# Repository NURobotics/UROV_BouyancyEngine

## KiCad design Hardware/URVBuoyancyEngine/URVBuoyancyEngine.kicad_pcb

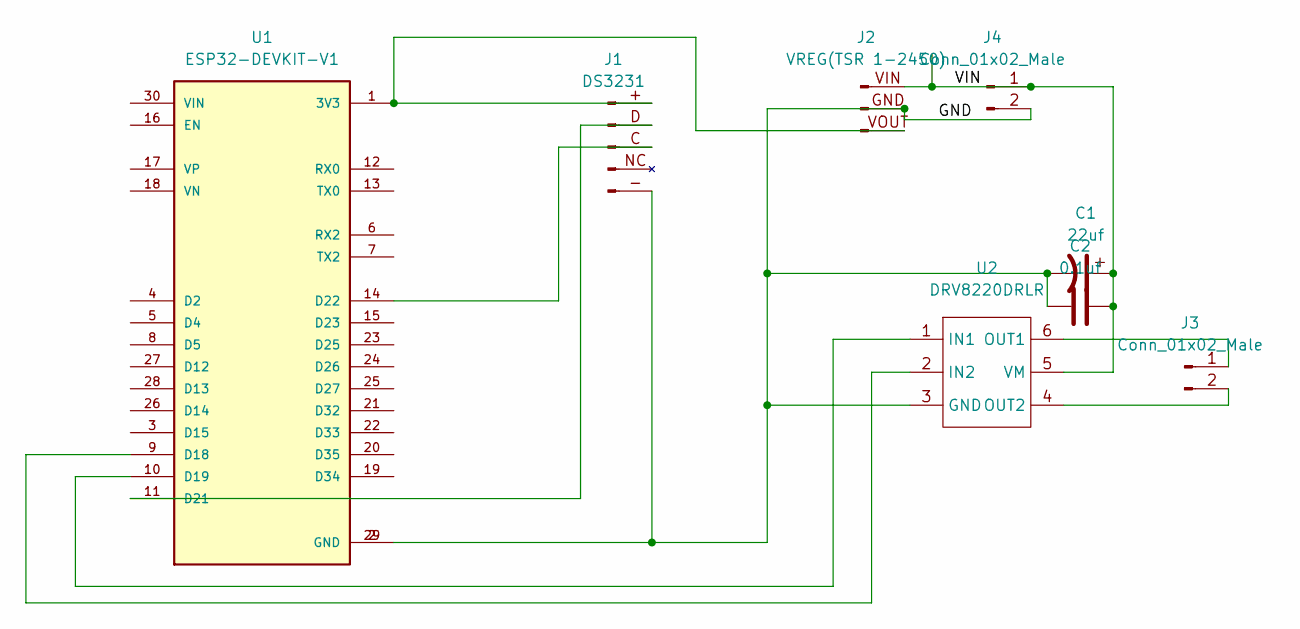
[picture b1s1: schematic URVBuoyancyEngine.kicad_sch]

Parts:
C1: 22uf; CP_Elec_5x5.7
C2: 0.1uf; C_0603_1608Metric
J1: DS3231; PinHeader_1x05_P2.54mm_Vertical
J2: VREG(TSR 1-2450); PinHeader_1x03_P2.54mm_Vertical
J3, J4: Conn_01x02_Male; PinHeader_1x02_P2.54mm_Vertical
U1: ESP32-DEVKIT-V1; MODULE_ESP32_DEVKIT_V1; PARTREV N/A
U2: DRV8220DRLR; SOT-563

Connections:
/GND: C1.2, C2.2, J1.- (5), J2.GND, J4.2, U1.2 (GND), U1.29 (GND), U2.3 (GND)
/VIN: C1.1, C2.1, J2.VIN, J4.1, U2.5 (VM)
unnamed: J1.+ (1), J2.VOUT, U1.1 (3V3)
unnamed: J1.C (3), U1.14 (D22)
unnamed: J1.D (2), U1.11 (D21)
unnamed: J3.1, U2.6 (OUT1)
unnamed: J3.2, U2.4 (OUT2)
unnamed: U1.9 (D18), U2.2 (IN2)
unnamed: U1.10 (D19), U2.1 (IN1)

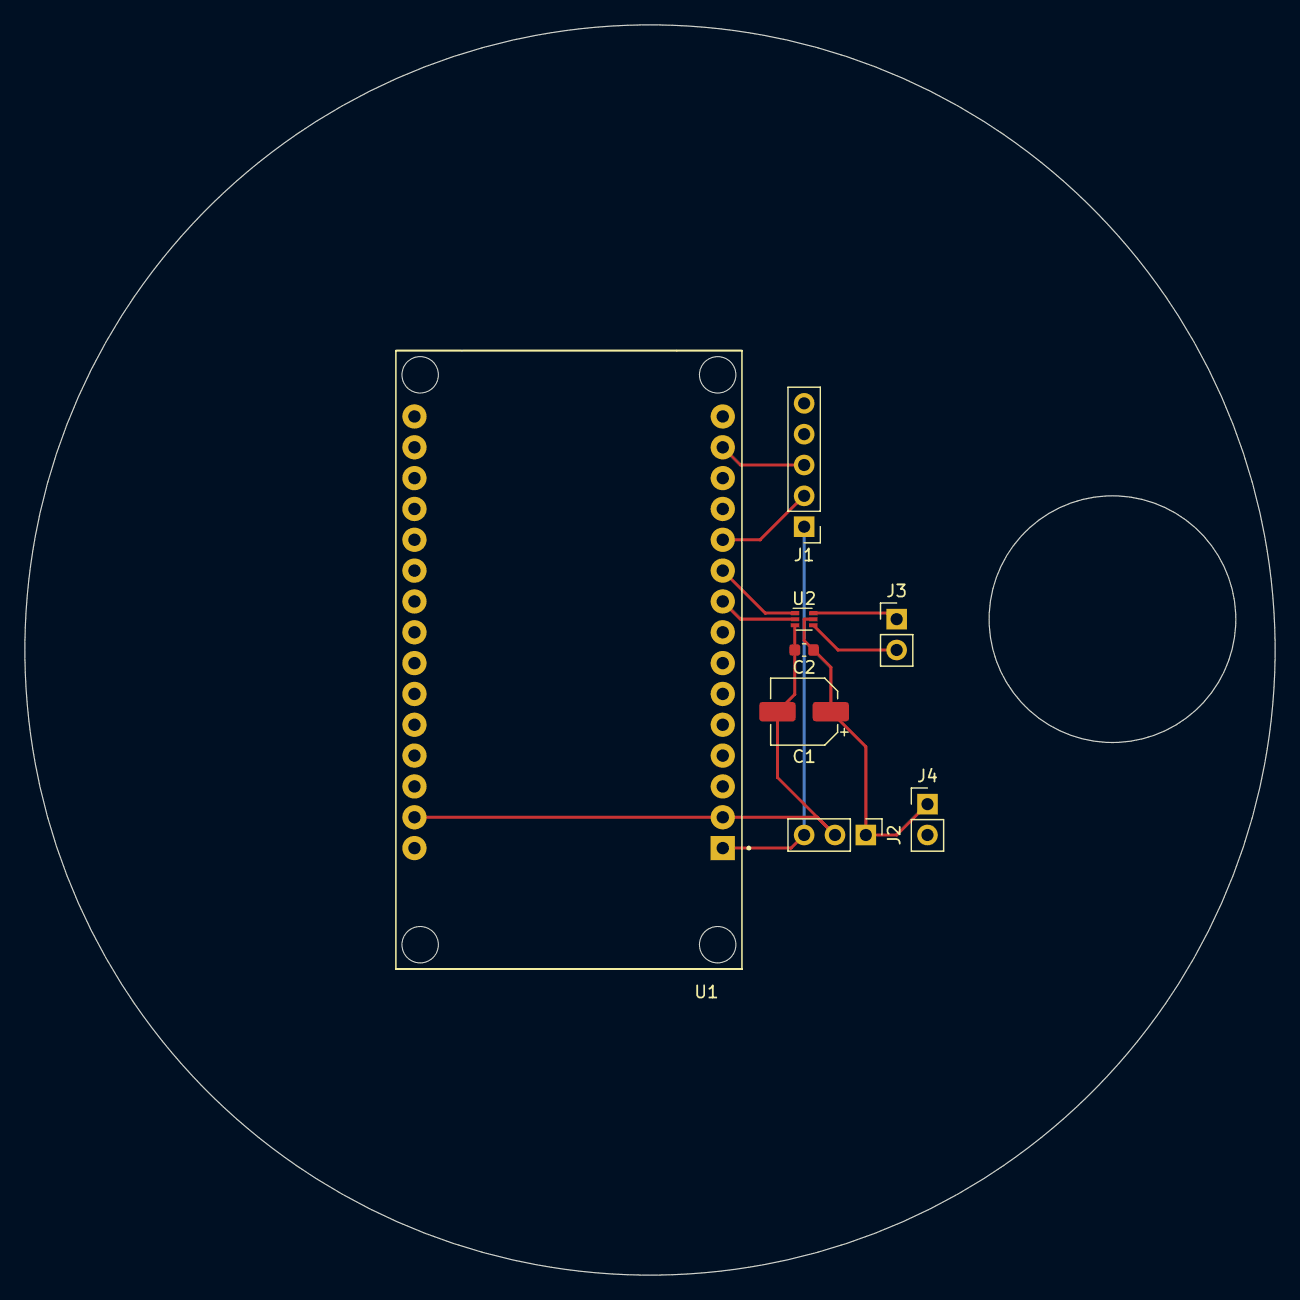
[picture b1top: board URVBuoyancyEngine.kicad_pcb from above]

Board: 2 copper layers, 103.0 x 103.0 mm, 8 parts (0 on the bottom side), 9 nets.

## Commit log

2022-11-20 Mostly working BT serial connection
2022-11-20 Changed a couple parameters, changed names
2022-12-14 BT transmit, recieve, screen work, buoyancy engine implemented with state machine but no actuation yet
2023-01-18 Buoyancy engine updates, PCB v1
